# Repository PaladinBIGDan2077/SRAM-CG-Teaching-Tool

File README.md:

## Members
Daniel J. Lomis, Computer Engineering: Chip-Scale Integration (May 2026)
dlomis1999@vt.edu

## Mentor
Professor Jason S. Thweatt

## Current Status
IN PROGRESS

## Project Overview

This project will demonstrate to the end-user how memory is used to store and read data within a computer, how changing BITs will have an effect on the output of a visualized character. while the unit itself will not be using a centralized processing unit instead the heart of the binary to ask you decoding will be controlled by a character generator ROM made by Fairchild semiconductor. The particular part is a 3257ADC from the late 1970s. The use of vintage components in this particular build helps to take away the layers of abstraction that computers now represent in modern day technology. By simplifying the underlying hardware that has the result of making the overall explanation of its functionality simpler. All plans were originally meant to include a set of early 1980s SRAM moudules. The need to switch to multiple education boards for the final product, made it clear that additional memory was needed as well as a more ample and stable supply of it.

## Educational Value Added

It provides insight to how character generator ROMs work, which were quite common in the days of early home computing. This will lead to a further understanding of ASCII based decoding. Storage of certain bits will allow the character rom to display individual characters on an LED Matrix, which will allow the viewer to write a message on screen letter by letter. A Binary Counter will be used to scroll through memory addresses, and a buffer will be used to display the current data to write to memory, as well as entry of a specific memory address.

## Tasks

Remaining tasks
 • research and implementation of a proper display method for the 8 x 8 matrix
 • research in limitation of the chosen memory modules
 • research and implementation of a binary input method for the memory
 • optional: an implementation to set and reset the memory counter to change specific memory areas that aren't linearly accessed

## Design Decisions

 • the board will be placed on a single PCB smaller than a sheet of standard letter paper
 • the device will be using a 16 VDC power supply going into the power connector on the board. The type of power supply and whether it will be USB-C based has yet to be determined.
 • 
## Design Misc

<!-- Your Text Here. You may work with your mentor on this later when they are assigned -->

## Steps for Documenting Your Design Process

<!-- Your Text Here. You may work with your mentor on this later when they are assigned -->

## BOM + Component Cost

VINTAGE Fairchild 3257ADC Character Generator ROM - $16.37
8X8 LED MATRIX - $10.86
VINTAGE AMD AM9101BPC SRAM Modules 256 x 4 BITS, (two used in series, two in parallel, to increase to 512 X 8 BITS) 512K RAM - $23.97

## Timeline

<!-- Your Text Here. You may work with your mentor on this later when they are assigned -->

## Useful Links

<!-- Your Text Here. You may work with your mentor on this later when they are assigned -->

## Log

<!-- Your Text Here. You may work with your mentor on this later when they are assigned -->

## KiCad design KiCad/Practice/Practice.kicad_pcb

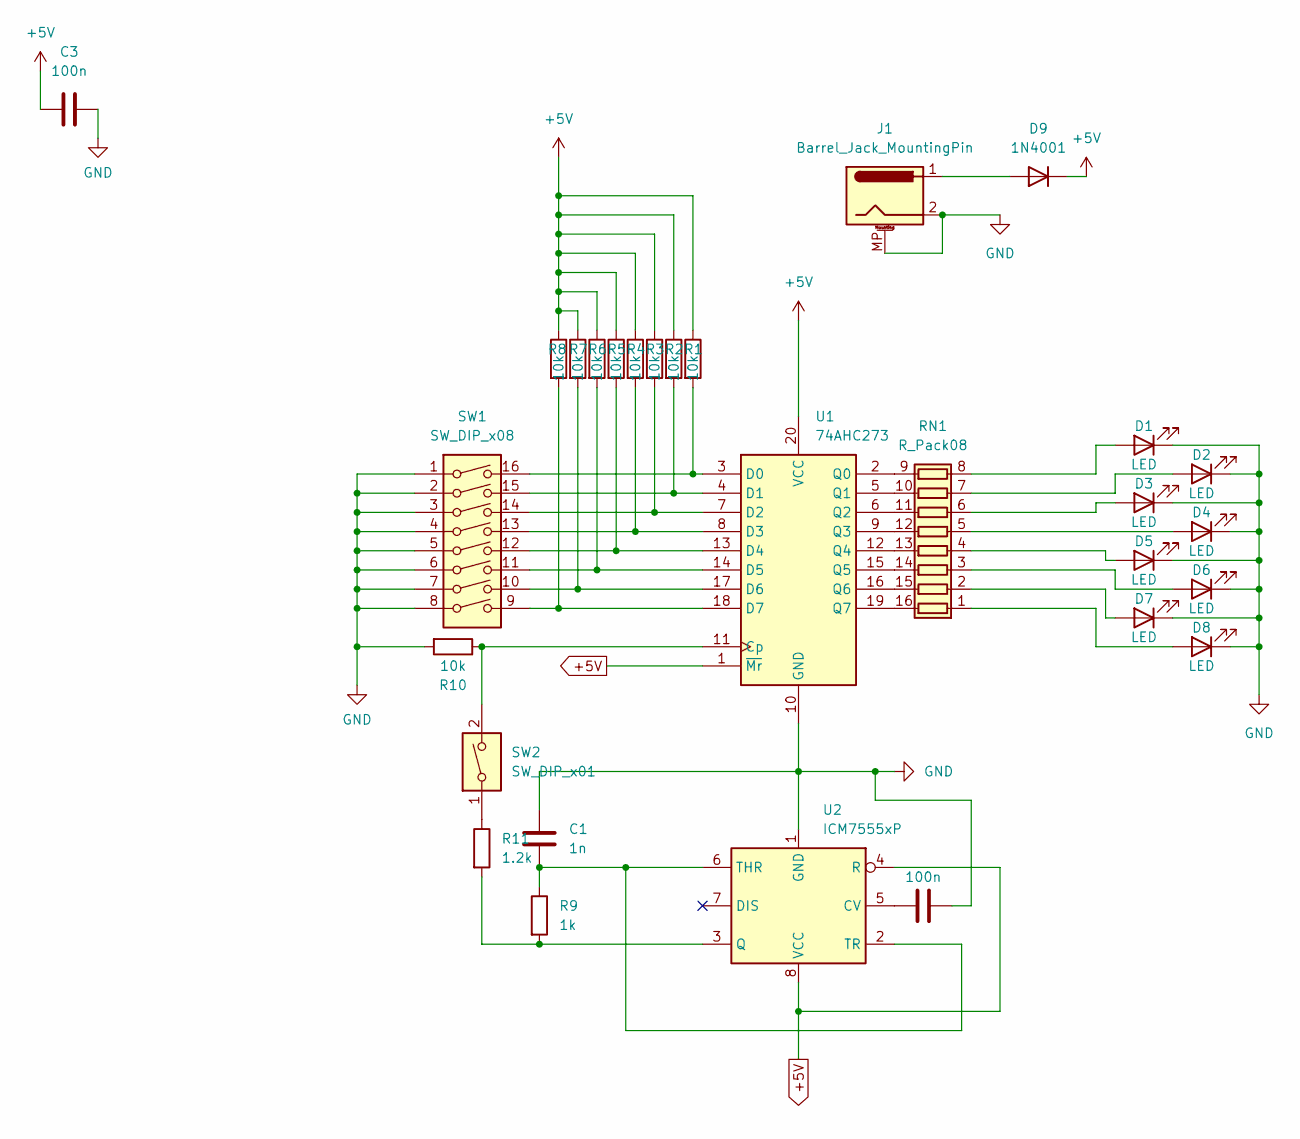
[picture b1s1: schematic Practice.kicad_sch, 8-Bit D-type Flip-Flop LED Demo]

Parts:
C1: 1n; C_Disc_D7.5mm_W2.5mm_P5.00mm
C2, C3: 100n; C_Disc_D7.5mm_W2.5mm_P5.00mm
D1, D2, D3, D4, D5, D6, D7, D8: LED; LED_D10.0mm
D9: 1N4001; D_DO-41_SOD81_P10.16mm_Horizontal
J1: Barrel_Jack_MountingPin; BarrelJack_CUI_PJ-063AH_Horizontal
R1, R2, R3, R4, R5, R6, R7, R8, R10: 10k; R_Axial_DIN0207_L6.3mm_D2.5mm_P7.62mm_Horizontal
R9: 1k; R_Axial_DIN0207_L6.3mm_D2.5mm_P7.62mm_Horizontal
R11: 1.2k; R_Axial_DIN0207_L6.3mm_D2.5mm_P7.62mm_Horizontal
RN1: R_Pack08; DIP-16_W7.62mm_Socket
SW1: SW_DIP_x08; SW_DIP_SPSTx08_Slide_9.78x22.5mm_W7.62mm_P2.54mm
SW2: SW_DIP_x01; SW_DIP_SPSTx01_Slide_9.78x4.72mm_W7.62mm_P2.54mm
U1: 74AHC273; DIP-20_W7.62mm_Socket
U2: ICM7555xP; DIP-8_W7.62mm_Socket

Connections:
+5V: C3.1, D9.1 (K), R1.1, R2.1, R3.1, R4.1, R5.1, R6.1, R7.1, R8.1, U1.1 (~Mr), U1.20 (VCC), U2.4 (R), U2.8 (VCC)
GND: C1.1, C2.2, C3.2, D1.1 (K), D2.1 (K), D3.1 (K), D4.1 (K), D5.1 (K), D6.1 (K), D7.1 (K), D8.1 (K), J1.2, J1.MP (MountPin), R10.2, SW1.1, SW1.2, SW1.3, SW1.4, SW1.5, SW1.6, SW1.7, SW1.8, U1.10 (GND), U2.1 (GND)
unnamed: D1.2 (A), RN1.8 (R8.1)
unnamed: D2.2 (A), RN1.7 (R7.1)
unnamed: D3.2 (A), RN1.6 (R6.1)
unnamed: D4.2 (A), RN1.5 (R5.1)
unnamed: D5.2 (A), RN1.4 (R4.1)
unnamed: D6.2 (A), RN1.3 (R3.1)
unnamed: D7.2 (A), RN1.2 (R2.1)
unnamed: D8.2 (A), RN1.1 (R1.1)
unnamed: D9.2 (A), J1.1
unnamed: R11.1, SW2.1
unnamed: RN1.16 (R1.2), U1.19 (Q7)
unnamed: RN1.15 (R2.2), U1.16 (Q6)
unnamed: RN1.14 (R3.2), U1.15 (Q5)
unnamed: RN1.13 (R4.2), U1.12 (Q4)
unnamed: RN1.12 (R5.2), U1.9 (Q3)
unnamed: RN1.11 (R6.2), U1.6 (Q2)
unnamed: RN1.10 (R7.2), U1.5 (Q1)
unnamed: RN1.9 (R8.2), U1.2 (Q0)
unnamed: R10.1, SW2.2, U1.11 (Cp)
unnamed: R1.2, SW1.16, U1.3 (D0)
unnamed: R2.2, SW1.15, U1.4 (D1)
unnamed: R3.2, SW1.14, U1.7 (D2)
unnamed: R4.2, SW1.13, U1.8 (D3)
unnamed: R5.2, SW1.12, U1.13 (D4)
unnamed: R6.2, SW1.11, U1.14 (D5)
unnamed: R7.2, SW1.10, U1.17 (D6)
unnamed: R8.2, SW1.9, U1.18 (D7)
unnamed: C2.1, U2.5 (CV)
unnamed: R9.2, R11.2, U2.3 (Q)
unnamed: C1.2, R9.1, U2.2 (TR), U2.6 (THR)

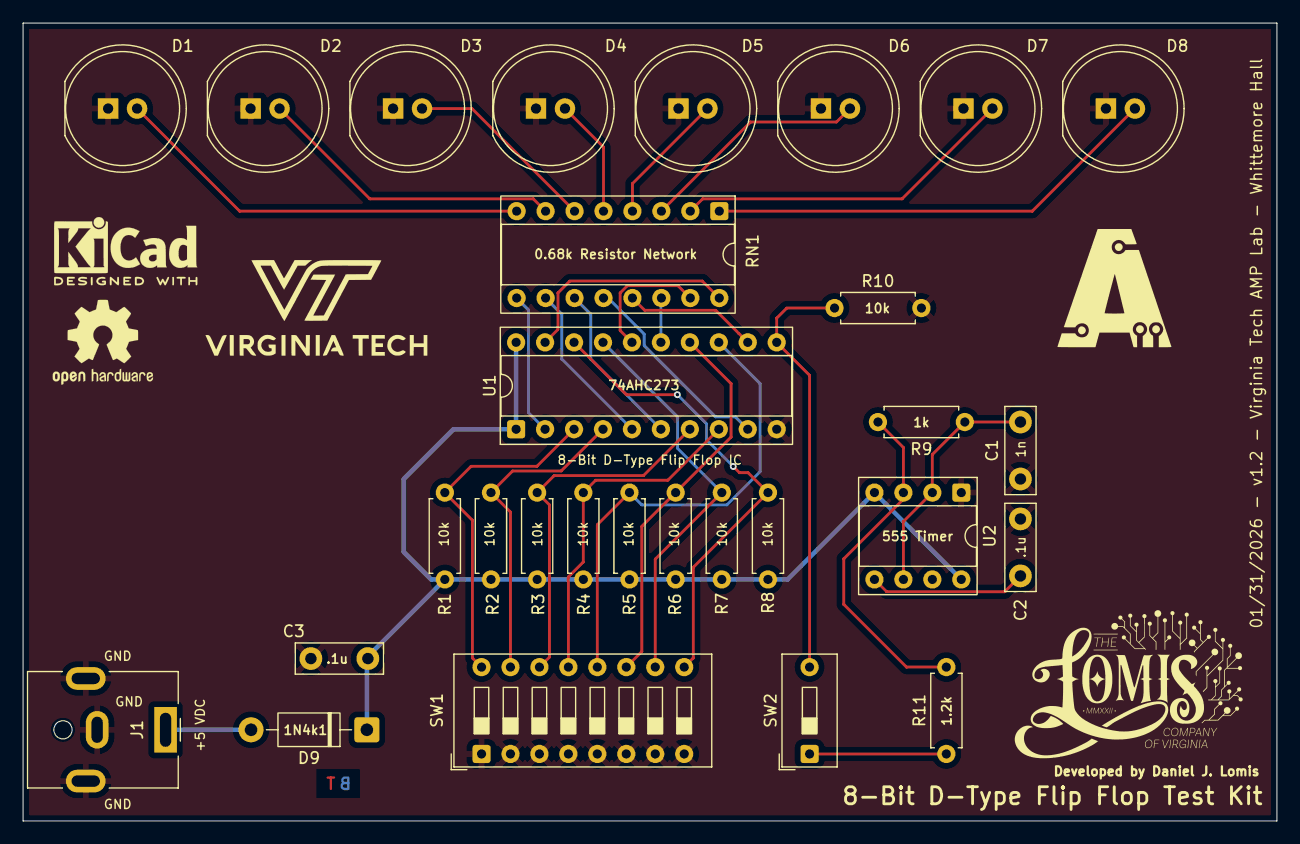
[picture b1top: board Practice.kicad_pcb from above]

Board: 4 copper layers, 110.0 x 70.0 mm, 29 parts (0 on the bottom side), 32 nets.

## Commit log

2025-09-21 Created first practice PCB
2025-09-21 Pushed further updates
2025-12-16 Development
2025-12-16 Trest
2026-01-29 Completed Raster Display for Project, still needs dialed in
2026-02-01 Development updates to the LED Demo D-Type Flip Flop Board
2026-03-09 Update README.md
    Updated description to reflect current progress of project
